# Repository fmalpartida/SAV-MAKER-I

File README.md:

# SAV-MAKER-I
## Introduction

The SAV MAKER I is an “open hardware” project made in Spain and based on the popular [vinciDuino board](https://bitbucket.org/fmalpartida/vinciduino/wiki/Home), 
predecessor of Arduino's Leonardo board and fully compatible with it. 
This development has been carried out for the Telecom Engineering "Applied Electronics" course carried out in the
UMA (Universidad de Málaga). On day one, students will receive a bare PCB and a set of components to assemble and 
use it on some of their course projects.

![SAV MAKER I Rev A] (https://github.com/fmalpartida/SAV-MAKER-I/blob/master/images/SAV%20MAKER%20I%20Rev%20A%20-%20PCBs.JPG)

The SAV MAKER I is an “open hardware” project, a board with an 8-bit microcontroller similar to the Arduino Leonardo
and fully compatible with it. The spirit behind it is for students to be able to build and user their own tools, 
analyse, build on and share their work.
At the end of the year, the board will be revised with their contributions, and who knows, we may use the highest rated board
on next year's course. It will be fun to see how the board evolves over the years.

Beign an open project where anyone can be part of the design team; anyone can bring knowledge, comments and ideas for 
developing other Arduino compatible training board or a programmable board using the Atmel environment without an 
external programmer. It is not limited to students. However, in comparison with other similar “open hardware” projects the 
SAV MAKER I has been designed for people to learn, build and use it while being cost effective. The cost has been optimized
as much as possible to accomodate any budget and pursue the real open hardware’s spirit.

## Wiki contents
* [SAV MAKER I wiki home](https://github.com/fmalpartida/SAV-MAKER-I/wiki)
* [Specifications](https://github.com/fmalpartida/SAV-MAKER-I/wiki/Specifications)
* [Board assembly and mechanical drawings](https://github.com/fmalpartida/SAV-MAKER-I/wiki/Mechanical-drawings-and-component-placement)
* [Board assembly step by step](https://github.com/fmalpartida/SAV-MAKER-I/wiki/Assembly-guide)

## Licensing
All information contained herein is licensed under [CERN OHL](http://www.ohwr.org/attachments/2388/cern_ohl_v_1_2.txt) (please refer to license file for details), so if someone 
wants to use this information to assemble kits, sell boards, etc. … feel free to do it.

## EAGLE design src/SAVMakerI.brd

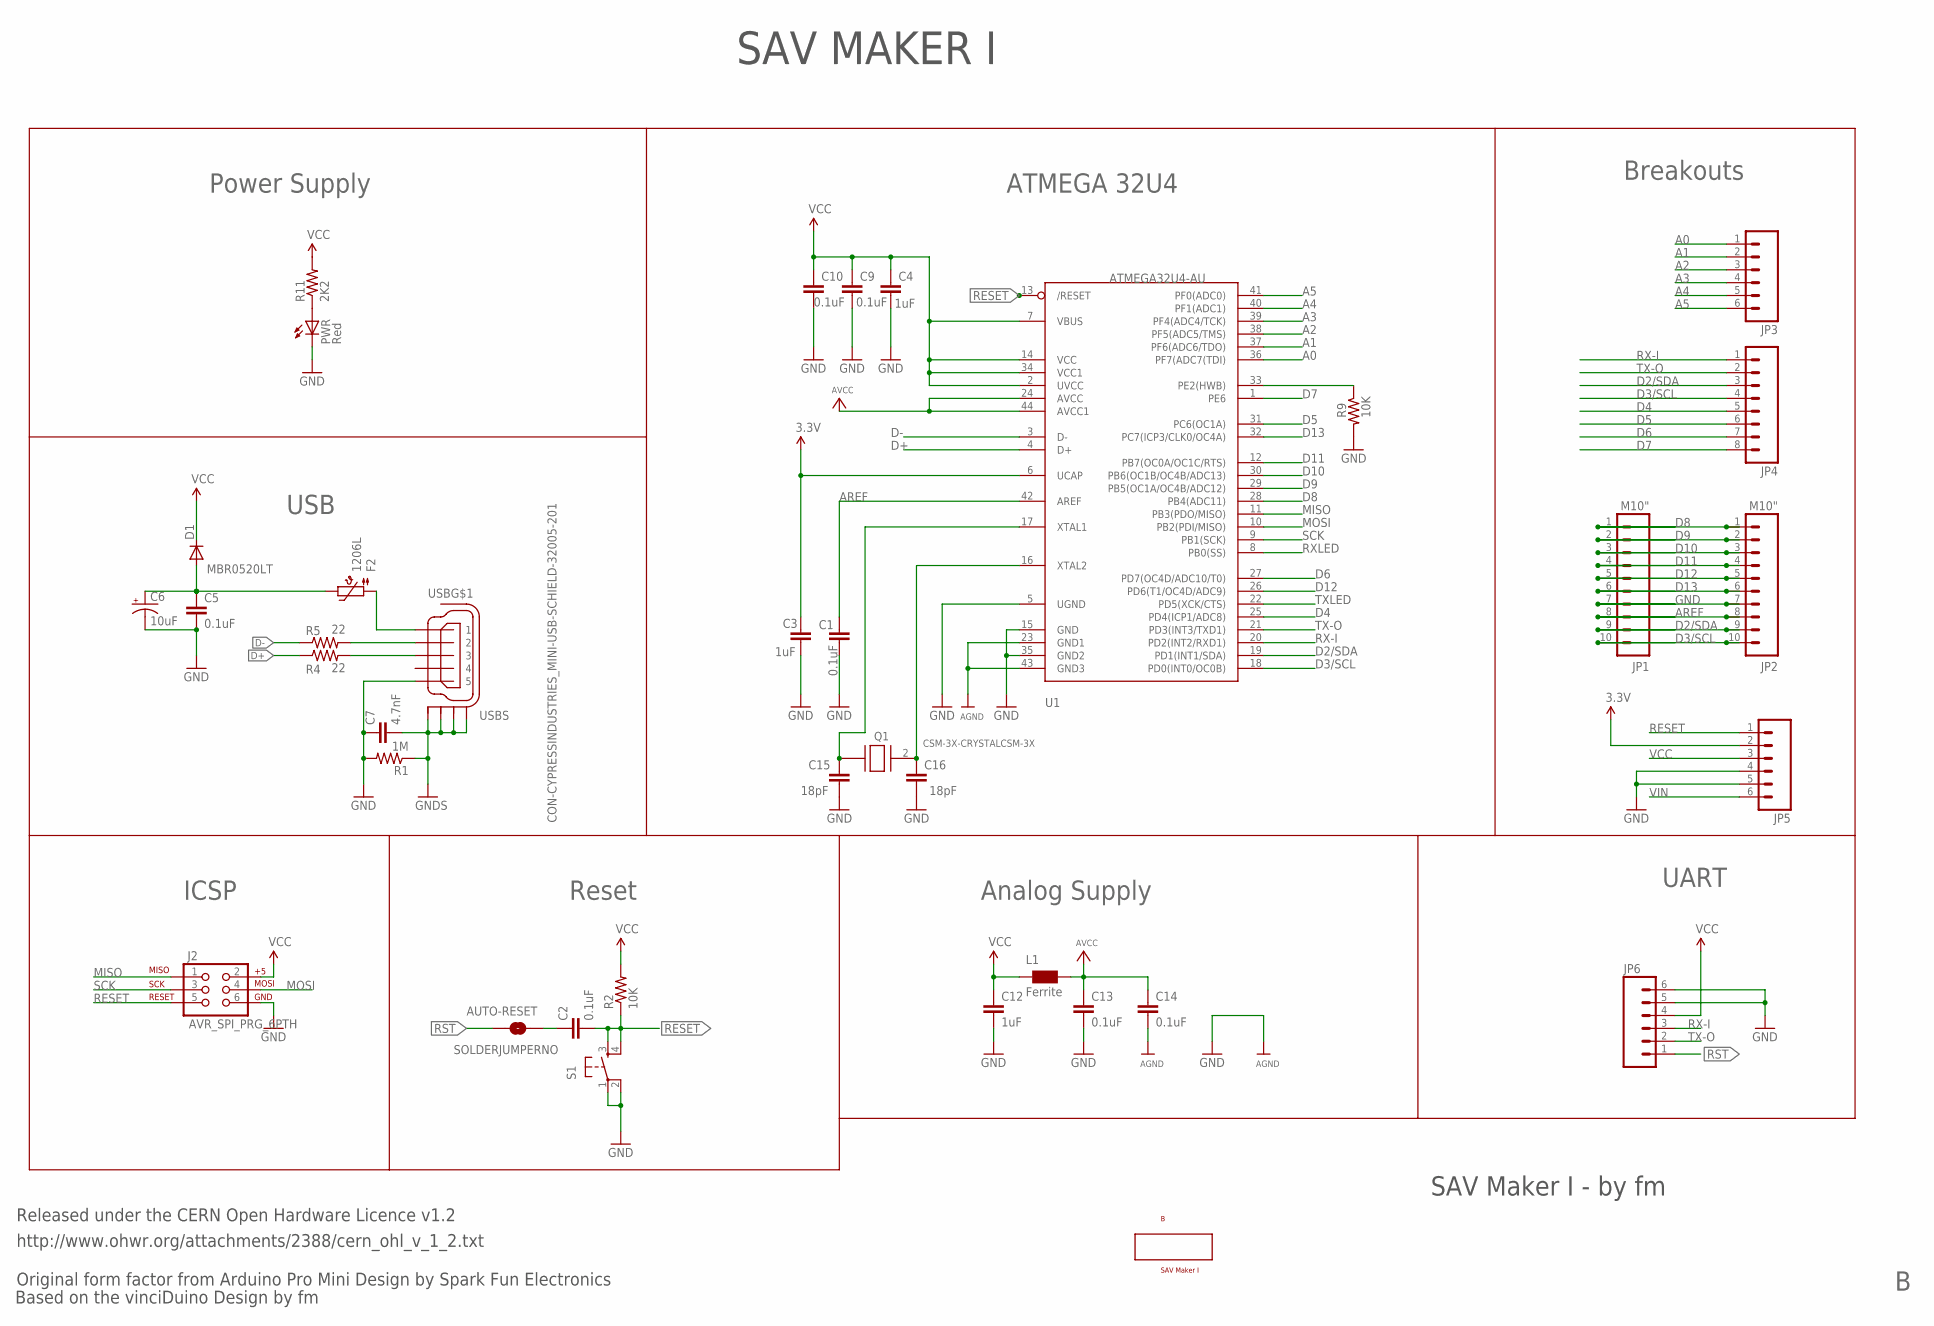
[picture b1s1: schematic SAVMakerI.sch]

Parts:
AUTO-RESET: SOLDERJUMPERNO; SJ_2S-NO
B: SAV Maker I; BOARD_INFO_BMP
C1, C2, C5, C9, C10, C13, C14: 0.1uF; 1206
C3, C4, C12: 1uF; 1206
C6: 10uF; EIA3216
C7: 4.7nF; 1206
C15, C16: 18pF; 1206
D1: MBR0520LT; SOD123
F2: 1206L; 1206_PTC
J2: AVR_SPI_PRG_6PTH; 2X3
JP1, JP2: M10"; 1X10
JP3, JP5, JP6: M06SIP; 1X06
JP4: M081X08; 1X08
L1: Ferrite; 1206W
PWR: Red; LED-1206
Q1: CSM-3X-CRYSTALCSM-3X; CSM-3X
R1: 1M; R1206
R2, R9: 10K; R1206
R4, R5: 22; R1206
R11: 2K2; R1206
S1: TAC_SWITCHSMD; TACTILE_SWITCH_SMD
U1: ATMEGA32U4-AU; ADAFRUIT_TQFP44
USB: CON-CYPRESSINDUSTRIES_MINI-USB-SCHIELD-32005-201; CON-CYPRESSINDUSTRIES_32005-201

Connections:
3.3V: C3.1, JP5.2, U1.6 (UCAP)
A0: JP3.1, U1.36 (PF7(ADC7(TDI))
A1: JP3.2, U1.37 (PF6(ADC6/TDO))
A2: JP3.3, U1.38 (PF5(ADC5/TMS))
A3: JP3.4, U1.39 (PF4(ADC4/TCK))
A4: JP3.5, U1.40 (PF1(ADC1))
A5: JP3.6, U1.41 (PF0(ADC0))
AREF: C1.2, JP1.8, JP2.8, U1.42 (AREF)
AVCC: C13.1, C14.1, L1.2, U1.24 (AVCC), U1.44 (AVCC1)
D2/SDA: JP1.9, JP2.9, JP4.3, U1.19 (PD1(INT1/SDA))
D3/SCL: JP1.10, JP2.10, JP4.4, U1.18 (PD0(INT0/OC0B))
D4: JP4.5, U1.25 (PD4(ICP1/ADC8))
D5: JP4.6, U1.31 (PC6(OC1A))
D6: JP4.7, U1.27 (PD7(OC4D/ADC10/T0))
D7: JP4.8, U1.1 (PE6)
D8: JP1.1, JP2.1, U1.28 (PB4(ADC11))
D9: JP1.2, JP2.2, U1.29 (PB5(OC1A/OC4B/ADC12))
D10: JP1.3, JP2.3, U1.30 (PB6(OC1B/OC4B/ADC13))
D11: JP1.4, JP2.4, U1.12 (PB7(OC0A/OC1C/RTS))
D12: JP1.5, JP2.5, U1.26 (PD6(T1/OC4D/ADC9))
D13: JP1.6, JP2.6, U1.32 (PC7(ICP3/CLK0/OC4A))
D+: R4.1, U1.4 (D+)
D-: R5.1, U1.3 (D-)
GND: C1.1, C3.2, C4.2, C5.2, C6.C (-), C7.1, C9.2, C10.2, C12.2, C13.2, C14.2, C15.2, C16.2, J2.6, JP1.7, JP2.7, JP5.4, JP5.5, JP6.5, JP6.6, PWR.C, R1.2, R9.2, S1.1, S1.2, U1.5 (UGND), U1.15 (GND), U1.23 (GND1), U1.35 (GND2), U1.43 (GND3), USB.5
GNDS: C7.2, R1.1, USB.M1 (S1), USB.M2 (S2), USB.M3 (S3), USB.M4 (S4)
MISO: J2.1, U1.11 (PB3(PDO/MISO))
MOSI: J2.4, U1.10 (PB2(PDI/MISO))
unnamed: R5.2, USB.2
unnamed: C16.1, Q1.2, U1.16 (XTAL2)
unnamed: C15.1, Q1.1, U1.17 (XTAL1)
unnamed: R4.2, USB.3
unnamed: R9.1, U1.33 (PE2(HWB))
unnamed: AUTO-RESET.2, C2.1
unnamed: F2.1, USB.1
unnamed: PWR.A, R11.1
RESET: C2.2, J2.5, JP5.1, R2.1, S1.3, S1.4, U1.13 (/RESET)
RST: AUTO-RESET.1, JP6.1
RX-I: JP4.1, JP6.3, U1.20 (PD2(INT2/RXD1))
RXLED: U1.8 (PB0(SS))
SCK: J2.3, U1.9 (PB1(SCK))
TX-O: JP4.2, JP6.2, U1.21 (PD3(INT3/TXD1))
TXLED: U1.22 (PD5(XCK/CTS))
VBUS: C5.1, C6.A (+), D1.A, F2.2
VCC: C4.1, C9.1, C10.1, C12.1, D1.C, J2.2, JP5.3, JP6.4, L1.1, R2.2, R11.2, U1.2 (UVCC), U1.7 (VBUS), U1.14 (VCC), U1.34 (VCC1)
VIN: JP5.6

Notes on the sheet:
Released under the CERN Open Hardware Licence v1.2
http://www.ohwr.org/attachments/2388/cern_ohl_v_1_2.txt
Original form factor from Arduino Pro Mini Design by Spark Fun Electronics
Based on the vinciDuino Design by fm
Power Supply
USB
Reset
ICSP
Analog Supply
UART
Breakouts
ATMEGA 32U4
SAV MAKER I
SAV Maker I - by fm

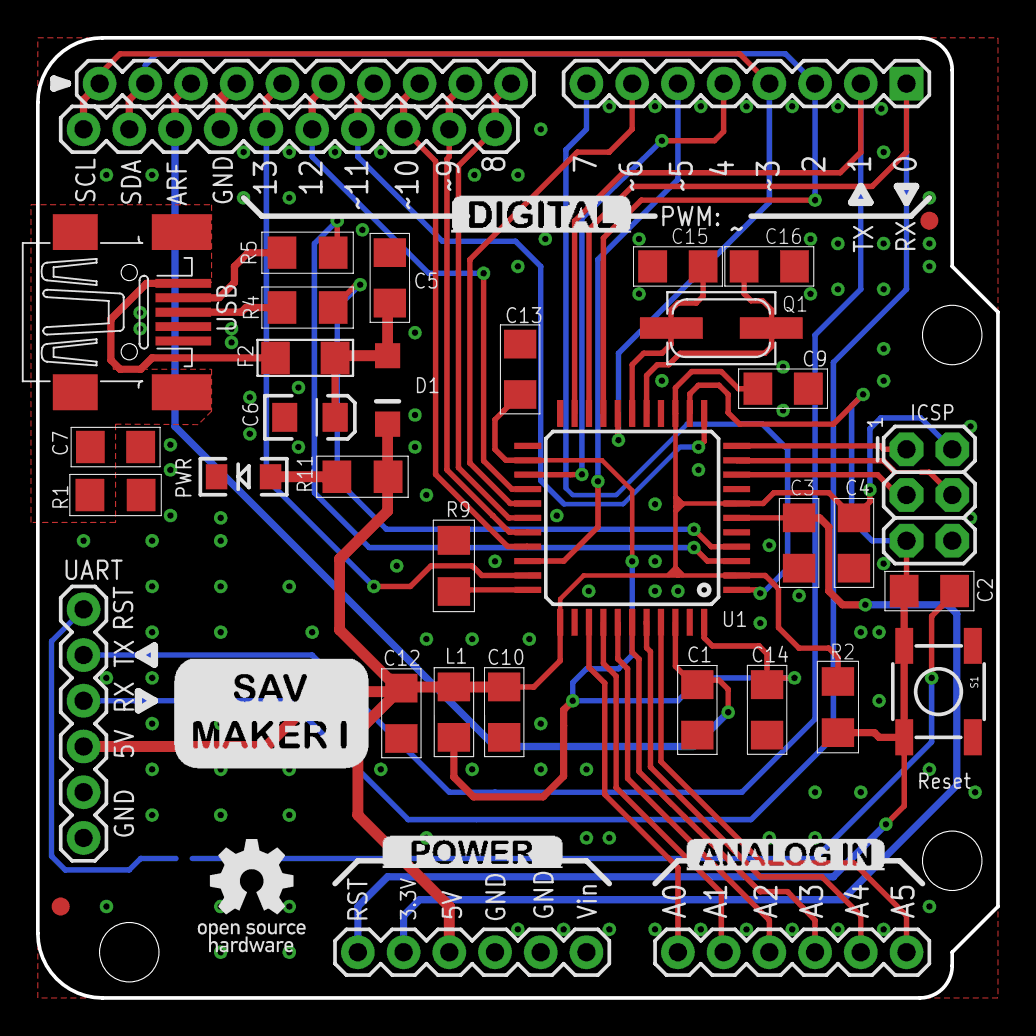
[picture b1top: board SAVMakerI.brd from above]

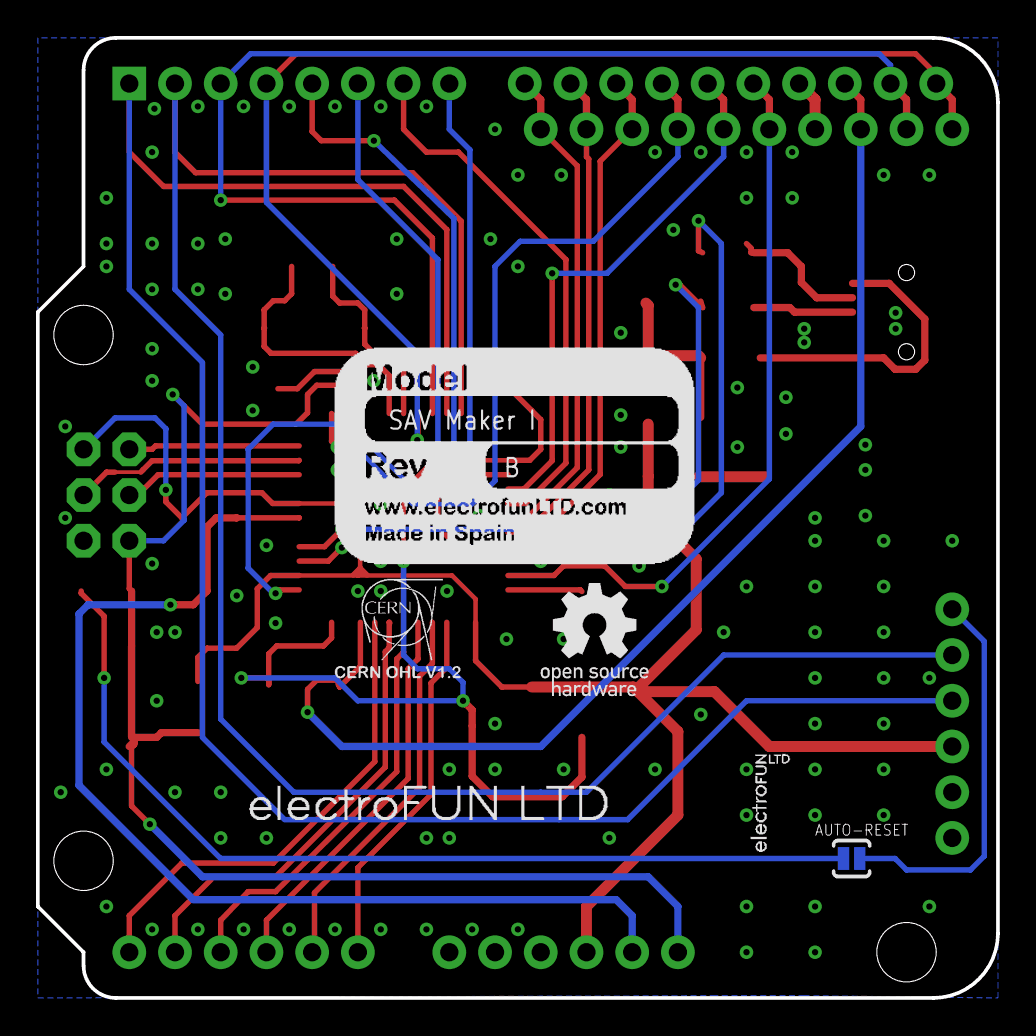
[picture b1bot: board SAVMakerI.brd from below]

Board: 2 copper layers, 53.3 x 53.3 mm, 50 parts (5 on the bottom side), 42 nets.

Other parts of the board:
U$1, U$3, U$5: STAND-OFF
U$2, U$4: FIDUCIAL1X2; FIDUCIAL-1X2
U$9: ELECTROFUN_STRIP
U$10: SAVMAKERI
U$13, U$15: OSHW
U$14: CERN_OHL
U$16: ANALOG_BMP
U$17: DIGITAL_BMP
U$18: POWER_BMP

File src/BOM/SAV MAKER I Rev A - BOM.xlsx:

Qty | Value | Parts | Device | Package | Description | Mouser part | Price | TOTAL
3 |  | JP3, JP5, JP6 | M06SIP | 1X06 | Header 6 |  |  | 0
1 |  | JP4 | M081X08 | 1X08 | Header 8 |  |  | 0
1 |  | S1 | TAC_SWITCHSMD | TACTILE_SWITCH_SMD | Momentary Switch | PTS525S | 0.23 | 0.23
7 | 0.1uF | C1, C2, C5, C9, C10, C13, C14 | CAP1206 | R1206 | Capacitor | VJ1206Y104KXXCW1BC | 2.8000000000000001E-2 | 0.19600000000000001
2 | 10K | R2, R9 | R-US_R1206 | R1206 | RESISTOR, American symbol | CRCW120610K0FKEA | 2.9000000000000001E-2 | 5.8000000000000003E-2
1 | 10uF | C6 | CAP_POL1206 | EIA3216 | Capacitor Polarized | F931A106MAA | 0.1 | 0.1
1 | 1206L | F2 | PTC1206_L | 1206_PTC | PTC (Resettable Fuse) | 504-PTS120616V025 | 0.28999999999999998 | 0.28999999999999998
1 | 1M | R1 | R-US_R1206 | R1206 | RESISTOR, American symbol | RC1206FR-071ML | 8.9999999999999993E-3 | 8.9999999999999993E-3
3 | 1uF | C3, C4, C12 | CAP1206 | R1206 | Capacitor | VJ1206Y105MXJTW1BC | 3.3000000000000002E-2 | 9.9000000000000005E-2
2 | 22R | R4, R5 | R-US_R1206 | R1206 | RESISTOR, American symbol | ERJ-8ENF22R0V | 1.9E-2 | 3.7999999999999999E-2
1 | 2K2 | R11 | R-US_R1206 | R1206 | RESISTOR, American symbol | CRCW12062K20JNEA | 1.2E-2 | 1.2E-2
1 | 4.7nF | C7 | CAP1206 | R1206 | Capacitor | VJ1206Y472KXXCW1BC | 0.03 | 0.03
1 | ATMEGA32U4-AU | U1 | ATMEGA32U4-AU | ADAFRUIT_TQFP44 | http://www.ladyada.net/library/eagle | ATMEGA32U4-AU | 4.91 | 4.91
1 | AVR_SPI_PRG_6PTH | J2 | AVR_SPI_PRG_6PTH | 2X3 | AVR ISP 6 Pin |  |  | 0
1 | MINI USB | USB | MINI-USB-SCHIELD-32005-201 | CON-CYPRESSINDUSTRIES_32005-201 | MINI USB-B Conector | 10033526-N3212LF | 0.54 | 0.54
1 | Ferrite | L1 | WE-CBF_1206W | 1206W | SMD EMI Suppression Ferrite Beads | 2512061027Y1 | 5.7000000000000002E-2 | 5.7000000000000002E-2
2 | M10";M10"" | Header 10 | 1X10 | JP1, JP2 |  |  |  | 0
1 | MBR0520LT | D1 | MBR0520LT | SOD123 | SCHOTTKY BARRIER RECTIFIER | MBR0520LT1G | 0.2 | 0.2
1 | RESONATORSMD | Y1 | RESONATORSMD | RESONATOR-SMD | Resonator | CSTCE16M0V53-R0 | 0.27400000000000002 | 0.27400000000000002
1 | Red | PWR | LED1206 | LED-1206 | LEDs | SML-LXF1206GC-TR | 0.09 | 0.09
1 | SAV Maker I | A | BOARD_INFO_BMP_20 | BOARD_INFO_BMP |  |  | 4.5 | 4.5
 |  |  |  |  |  |  | TOTAL | 11.633000000000001

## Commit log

2015-08-20 Create README.md
    First version of the readme file.
2015-08-20 First public version of the board.
2015-08-20 Added PDF schematic and board 3D renders.
2015-08-20 Added renders and images to the repo.
2015-08-20 Added mechanical and assembly guide.
2015-08-20 Update README.md
    Added board assembly information.
2015-09-06 Added board characteristics.
2015-09-07 Added electrical performance electrical characteristics.
2015-09-07 Added test firmware to check board's assembly.
2015-11-02 first image for the assembly guide
    This is an example of image uploaded to the repository for embeding them
    in the assembly guide wiki
2015-11-03 /Users/MYN/Documents/UMA/Creativa/SAVMAKERI/imagen2.JPG
    A ver si funciona
2015-11-03 /Users/MYN/Documents/UMA/Creativa/SAVMAKERI/imagen2.JPG
    Estoy probando a ver si puedo subir la imagen
2015-11-03 Creo que estoy cerca
    /Users/MYN/Documents/UMA/Creativa/SAVMAKERI/imagen2.JPG
2015-11-03 Espero que sí
    /Users/MYN/Documents/UMA/Creativa/SAVMAKERI/imagen2.JPG
2015-11-03 Prueba
    Es una prueba para subir una imagen.
2015-11-03 BIN /Users/MYN/Documents/UMA/Creativa/SAVMAKERI/imagen2.JPG
2015-11-03 Prueba de adición de fotos
    A ver si ahora sí...
2015-11-03 Nuevas imágenes
    Imágenes para la guía
2015-11-03 Added photos to assembly guide.
2015-11-09 Added assembly guide PDF
2015-11-09 Old assembly guide removed. Added new assembly guide.
2015-11-10 New folder with all things about assembly guide. Removed duplicated photos.
2015-11-26 primer fichero de prueba
2015-11-27 Adding 3D models
    SAV MAKER I 3d model housing
2015-11-29 Update 1
    Changes in the pin holes and some adjustments to fit them well the top
    and bottom parts.
2016-08-18 Added oscillator replacing the resonator.
2016-08-18 Uploaded gerber files.
2016-08-18 Minor modifications to routes.
2016-08-18 Updated routing.
2016-08-18 Updated documentation: schematic and 3D renders.
2016-08-22 Updated placement and schematic.
2016-08-23 Empty assembly gude removed from src folder
    this was a student try
2016-08-23 Layout and assemby images reorganized according to Rev
    Even if this is just for the wiki, it was a bit messy and could be
    confusing
2016-08-23 Updated mirrored file.
2016-09-25 Added support for Platform IO projects.
2016-10-26 Added images PCB RevB top and bottom assembled.
2016-10-27 InstallingBootloader
